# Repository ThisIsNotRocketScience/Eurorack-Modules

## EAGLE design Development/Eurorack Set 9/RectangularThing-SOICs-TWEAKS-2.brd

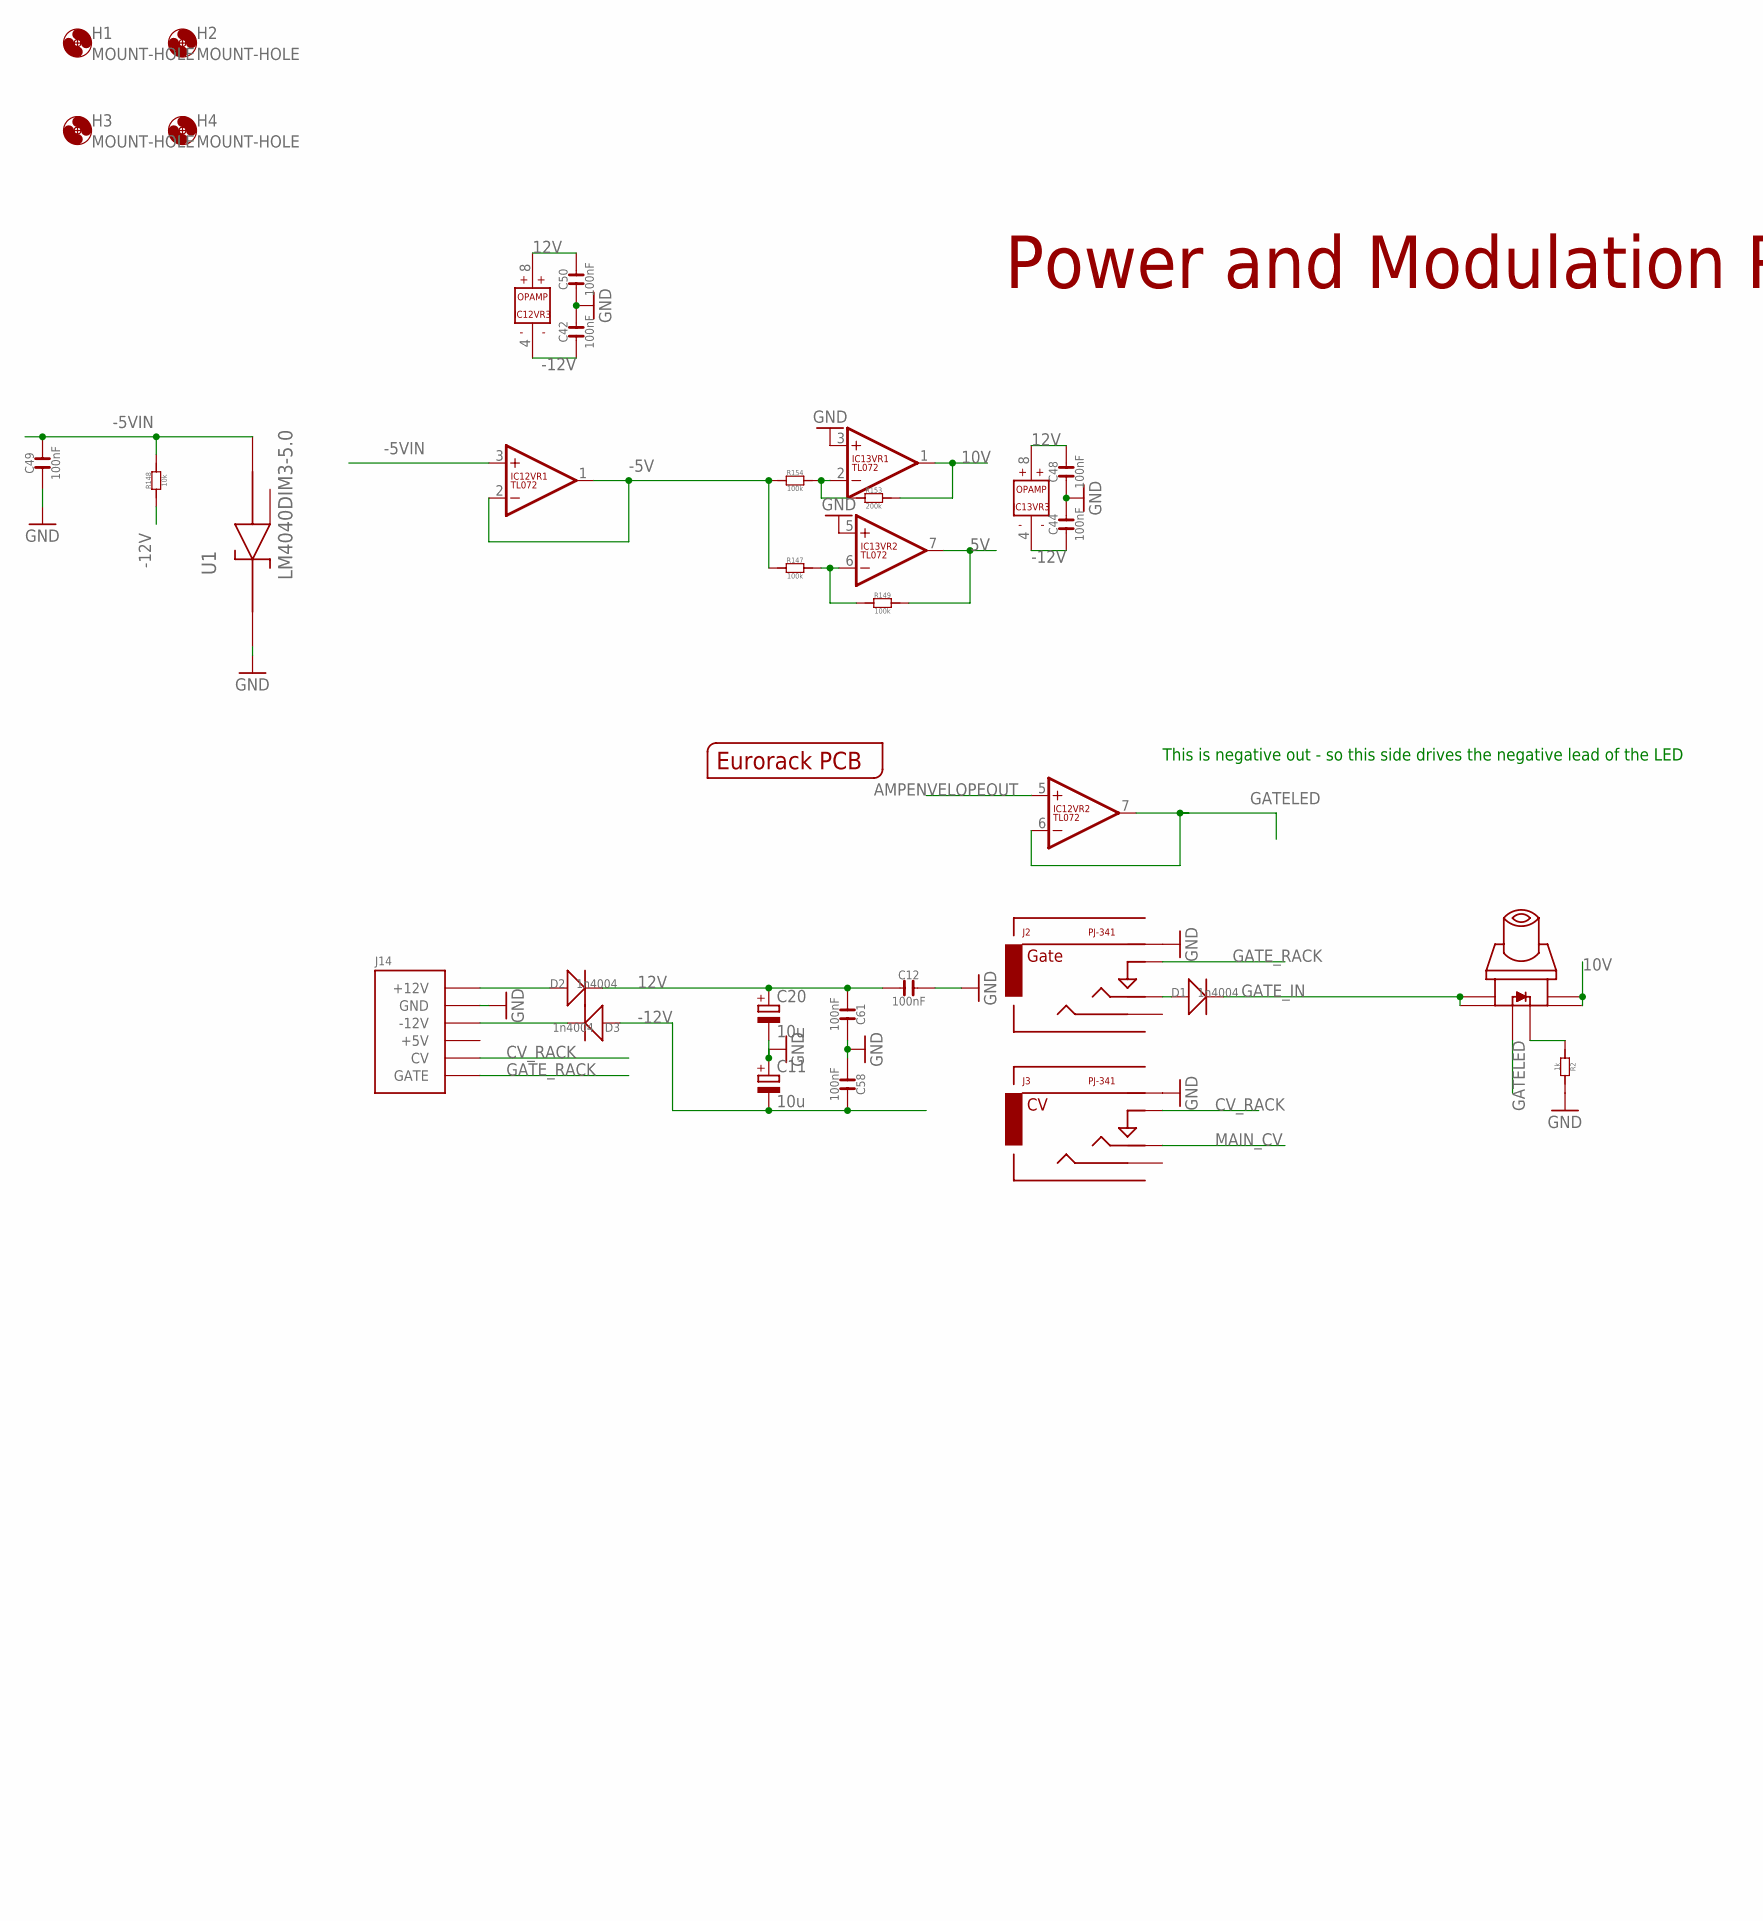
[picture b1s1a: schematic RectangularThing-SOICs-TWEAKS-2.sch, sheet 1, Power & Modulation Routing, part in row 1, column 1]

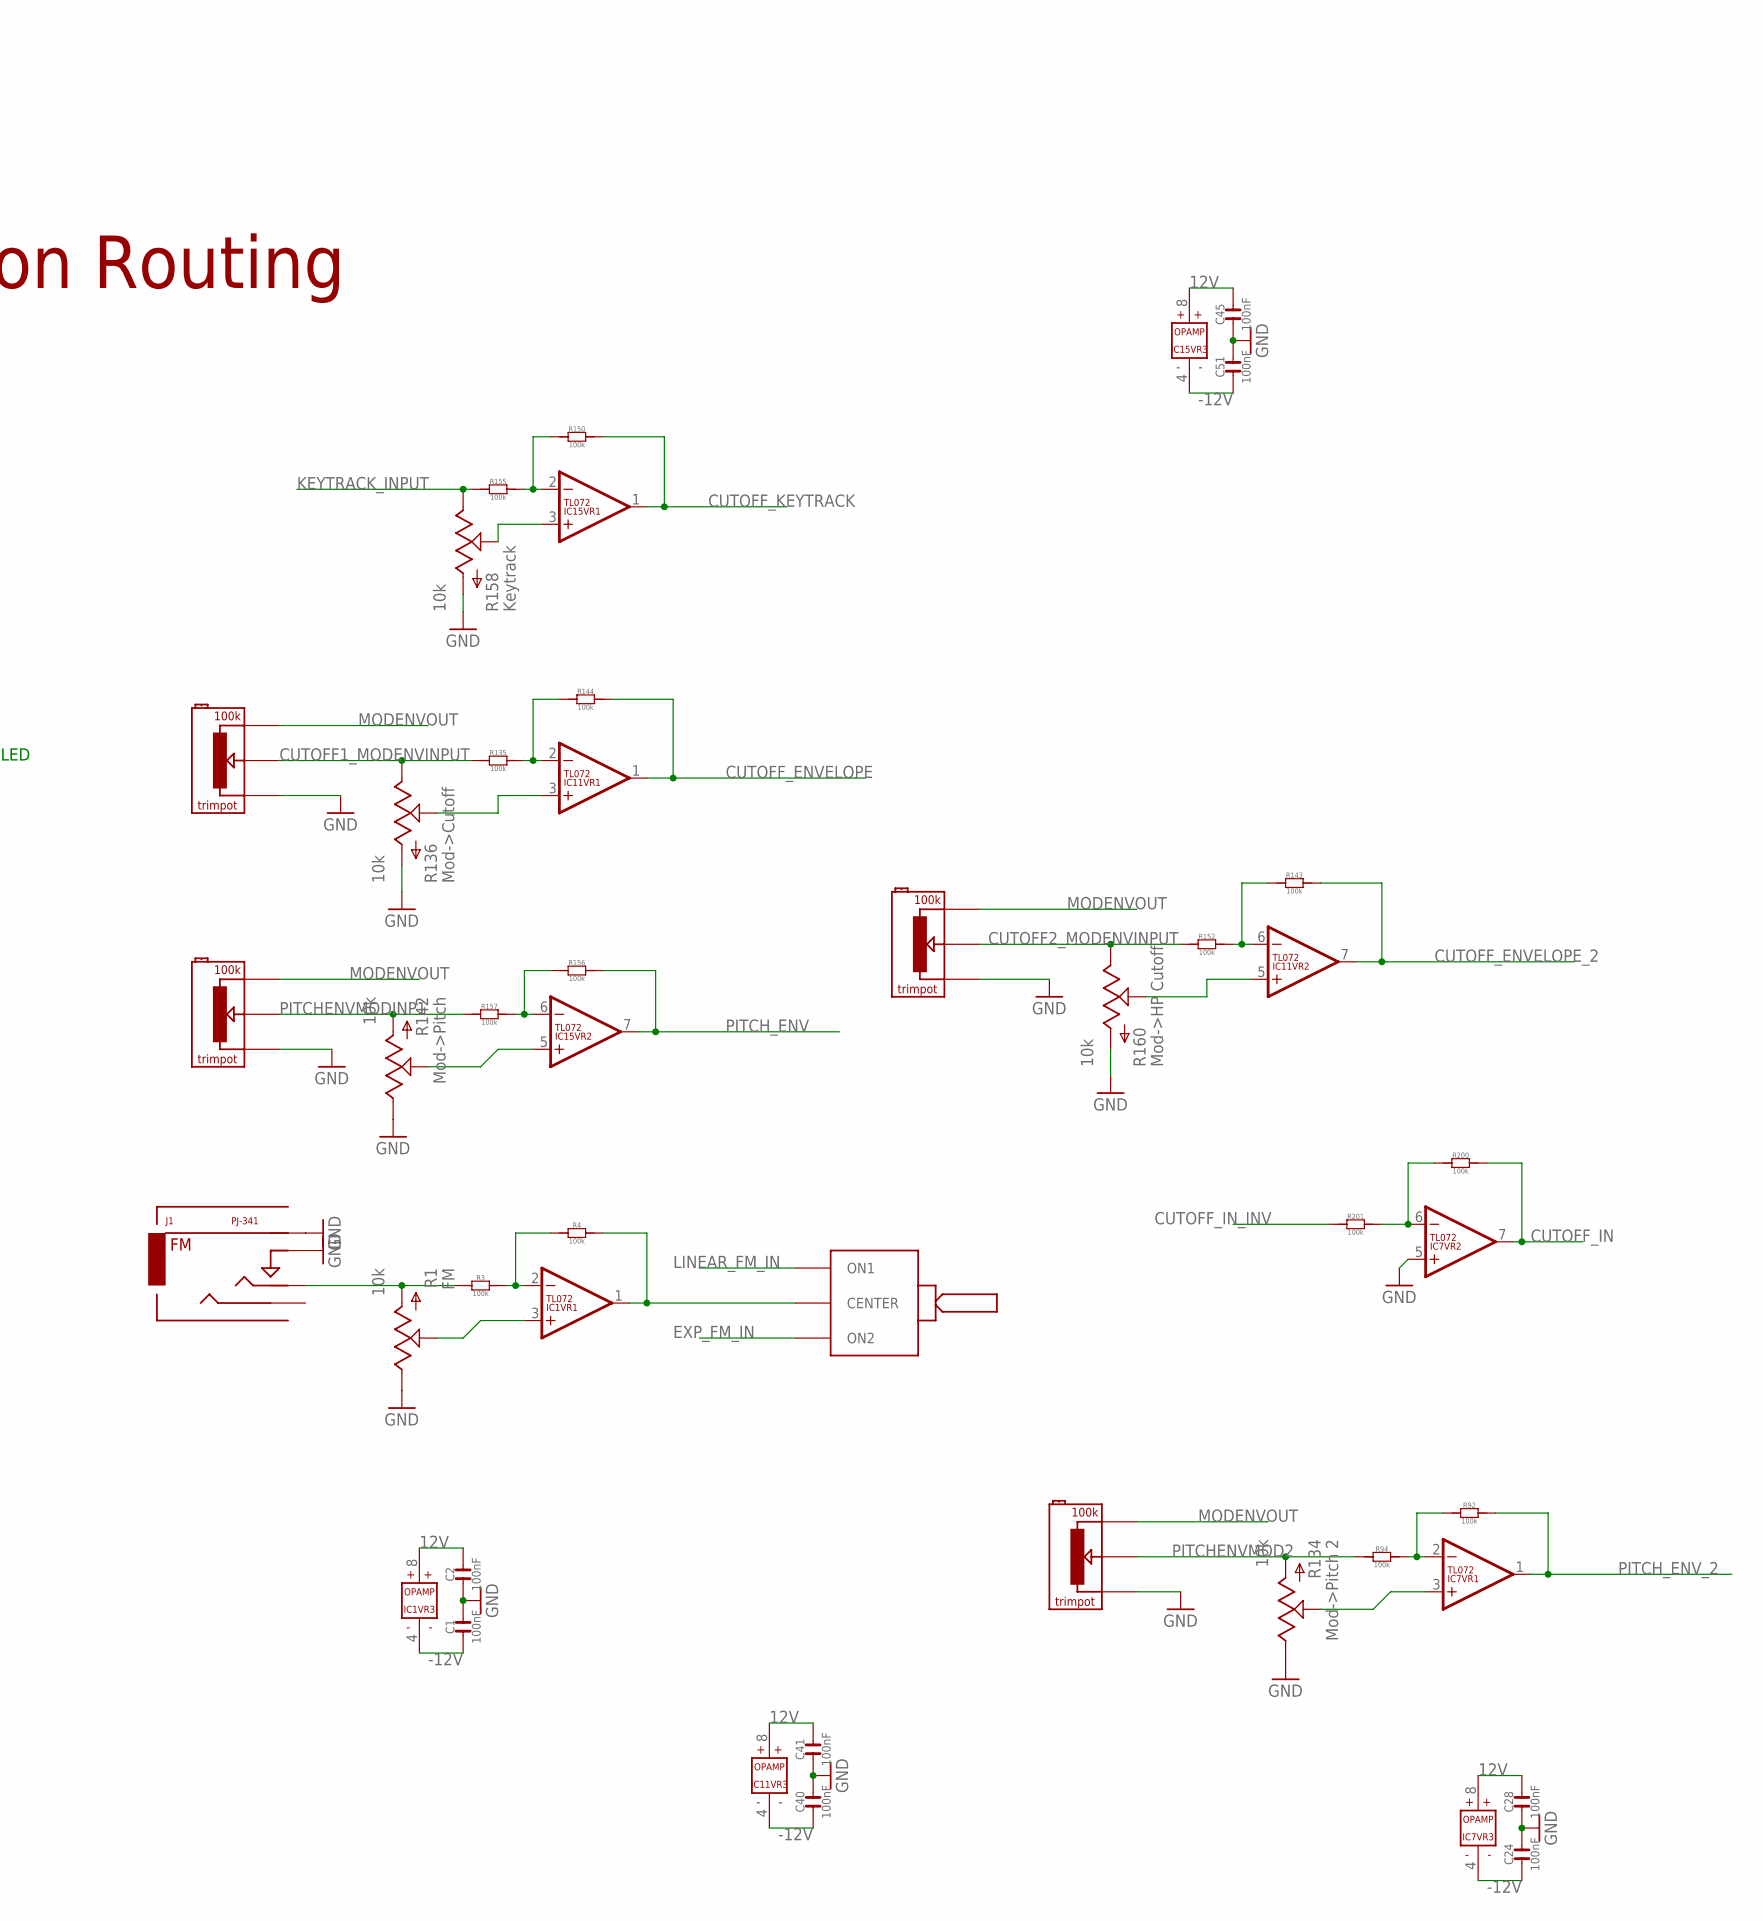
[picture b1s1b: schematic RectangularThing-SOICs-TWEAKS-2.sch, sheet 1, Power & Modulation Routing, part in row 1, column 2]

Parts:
C1, C2, C12, C24, C28, C40, C41, C42, C44, C45, C48, C50, C51, C58, C61: 100nF; C0603
C11, C20: 10u; CASE_B
C49: 100nF; C0603; MPN 06035C104KAT2A
D1, D2, D3: 1n4004; DO-214AC
H1, H2, H3, H4: MOUNT-HOLE; 3.2-NOMARKINGS-SMALLSAFEZONE
IC1, IC7, IC11, IC12, IC13, IC15: TL072; SO08
J1, J2, J3: PJ-341; 3.5MM-JACK-SWITCH-13MM-INPUT
J14: POWERSHROUDED; POWER_16_SHROUDED
PCB1: EURORACK_PCB36HP_10CM; EURORACK36HP
R1, R134, R136, R142, R158, R160: 10k; OG-POTS_ALPS_POT_VERTICAL
R2: 1k; R0603
R3, R4, R92, R94, R135, R143, R144, R147, R149, R150, R152, R154, R155, R156, R157, R200, R201: 100k; R0603
R148: 10k; R0603
R153: 200k; R0603
R191, R192, R193, R194: 100k; TRIMPOT
S1: ONOFFON; MULTICOMP1MS-ONOFFON
S2: SWITCH_W_LED_PB6149L-X-102YELLOW; PB6149L
U1: LM4040DIM3-5.0; SOT95P237X112-3N

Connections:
5V: IC13.7 (OUT), R149.2; also elsewhere on the board
10V: IC13.1 (OUT), R153.2, S2.3, S2.4; also elsewhere on the board
12V: C2.2, C12.1, C20.+, C28.2, C41.2, C45.2, C48.2, C50.2, C61.1, D2.2 (-), IC1.8 (V+), IC7.8 (V+), IC11.8 (V+), IC12.8 (V+), IC13.8 (V+), IC15.8 (V+); also elsewhere on the board
-5V: IC12.1 (OUT), IC12.2 (-IN), R147.1, R154.1; also elsewhere on the board
-5VIN: C49.2, IC12.3 (+IN), R148.2, U1.2 (ANODE)
-5V_TO_5V: IC13.6 (-IN), R147.2, R149.1
-5_TO_10V: IC13.2 (-IN), R153.1, R154.2
-12V: C1.1, C11.-, C24.1, C40.1, C42.1, C44.1, C51.1, C58.2, D3.1 (+), IC1.4 (V-), IC7.4 (V-), IC11.4 (V-), IC12.4 (V-), IC13.4 (V-), IC15.4 (V-), R148.1; also elsewhere on the board
AMPENVELOPEOUT: IC12.5 (+IN); also elsewhere on the board
CUTOFF1_MODENVINPUT: R135.1, R136.P$1 (E), R192.P$2
CUTOFF2_MODENVINPUT: R152.1, R160.P$1 (E), R194.P$2
CUTOFF_ENVELOPE: IC11.1 (OUT), R144.2; also elsewhere on the board
CUTOFF_ENVELOPE_2: IC11.7 (OUT), R143.2; also elsewhere on the board
CUTOFF_IN: IC7.7 (OUT), R200.2; also elsewhere on the board
CUTOFF_IN_INV: R201.1; also elsewhere on the board
CUTOFF_KEYTRACK: IC15.1 (OUT), R150.2; also elsewhere on the board
CV_RACK: J3.SWITCH@3 (SWITCH), J14.13 (CV), J14.14 (CV)
EXP_FM_IN: S1.3 (ON2); also elsewhere on the board
GATELED: IC12.6 (-IN), IC12.7 (OUT), S2.LEDPOS (POS)
GATE_IN: D1.2 (-), S2.1, S2.2; also elsewhere on the board
GATE_RACK: J2.SWITCH@3 (SWITCH), J14.15 (GATE), J14.16 (GATE)
GND: C1.2, C2.1, C11.+, C12.2, C20.-, C24.2, C28.1, C40.2, C41.1, C42.2, C44.2, C45.1, C48.1, C49.1, C50.1, C51.2, C58.1, C61.2, IC7.5 (+IN), IC13.3 (+IN), IC13.5 (+IN), J1.RING@3 (RING), J1.SWITCH@3 (SWITCH), J2.RING@3 (RING), J3.RING@3 (RING), J14.3 (GND), J14.4 (GND), J14.5 (GND), J14.6 (GND), J14.7 (GND), J14.8 (GND), R1.P$1 (E), R2.2, R134.P$1 (E), R136.P$3 (A), R142.P$1 (E), R158.P$3 (A), R160.P$3 (A), R191.P$1, R192.P$1, R193.P$1, R194.P$1, U1.1 (CATHODE); also elsewhere on the board
KEYTRACK_INPUT: R155.1, R158.P$1 (E); also elsewhere on the board
LINEAR_FM_IN: S1.1 (ON1); also elsewhere on the board
MAIN_CV: J3.TIP@3 (TIP); also elsewhere on the board
MODENVOUT: R191.P$3, R192.P$3, R193.P$3, R194.P$3; also elsewhere on the board
unnamed: D2.1 (+), J14.9 (+12V), J14.10 (+12V)
unnamed: D3.2 (-), J14.1 (-12V), J14.2 (-12V)
unnamed: R2.1, S2.LEDNEG (NEG)
unnamed: IC1.1 (OUT), R4.2, S1.2 (CENTER)
unnamed: IC1.2 (-IN), R3.2, R4.1
unnamed: IC15.2 (-IN), R150.1, R155.2
unnamed: IC15.3 (+IN), R158.P$2 (S)
unnamed: IC11.2 (-IN), R135.2, R144.1
unnamed: IC15.6 (-IN), R156.1, R157.2
unnamed: IC11.3 (+IN), R136.P$2 (S)
unnamed: IC7.2 (-IN), R92.1, R94.2
unnamed: IC7.3 (+IN), R134.P$2 (S)
unnamed: IC15.5 (+IN), R142.P$2 (S)
unnamed: IC1.3 (+IN), R1.P$2 (S)
unnamed: J1.TIP@3 (TIP), R1.P$3 (A), R3.1
unnamed: D1.1 (+), J2.TIP@3 (TIP)
unnamed: IC11.6 (-IN), R143.1, R152.2
unnamed: IC11.5 (+IN), R160.P$2 (S)
unnamed: IC7.6 (-IN), R200.1, R201.2
PITCHENVMOD2: R94.1, R134.P$3 (A), R191.P$2
PITCHENVMODINP1: R142.P$3 (A), R157.1, R193.P$2
PITCH_ENV: IC15.7 (OUT), R156.2; also elsewhere on the board
PITCH_ENV_2: IC7.1 (OUT), R92.2; also elsewhere on the board

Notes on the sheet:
This is negative out - so this side drives the negative lead of the LED
Power and Modulation Routing

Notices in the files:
parts and their libraries:
SparkFun-Passives: Licensing: CC v3.0 Share-Alike You are welcome to use this library for commercial purposes.
